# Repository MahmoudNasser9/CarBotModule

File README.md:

"# CarBotModule" 

<!-- Car Bot Moduls -->

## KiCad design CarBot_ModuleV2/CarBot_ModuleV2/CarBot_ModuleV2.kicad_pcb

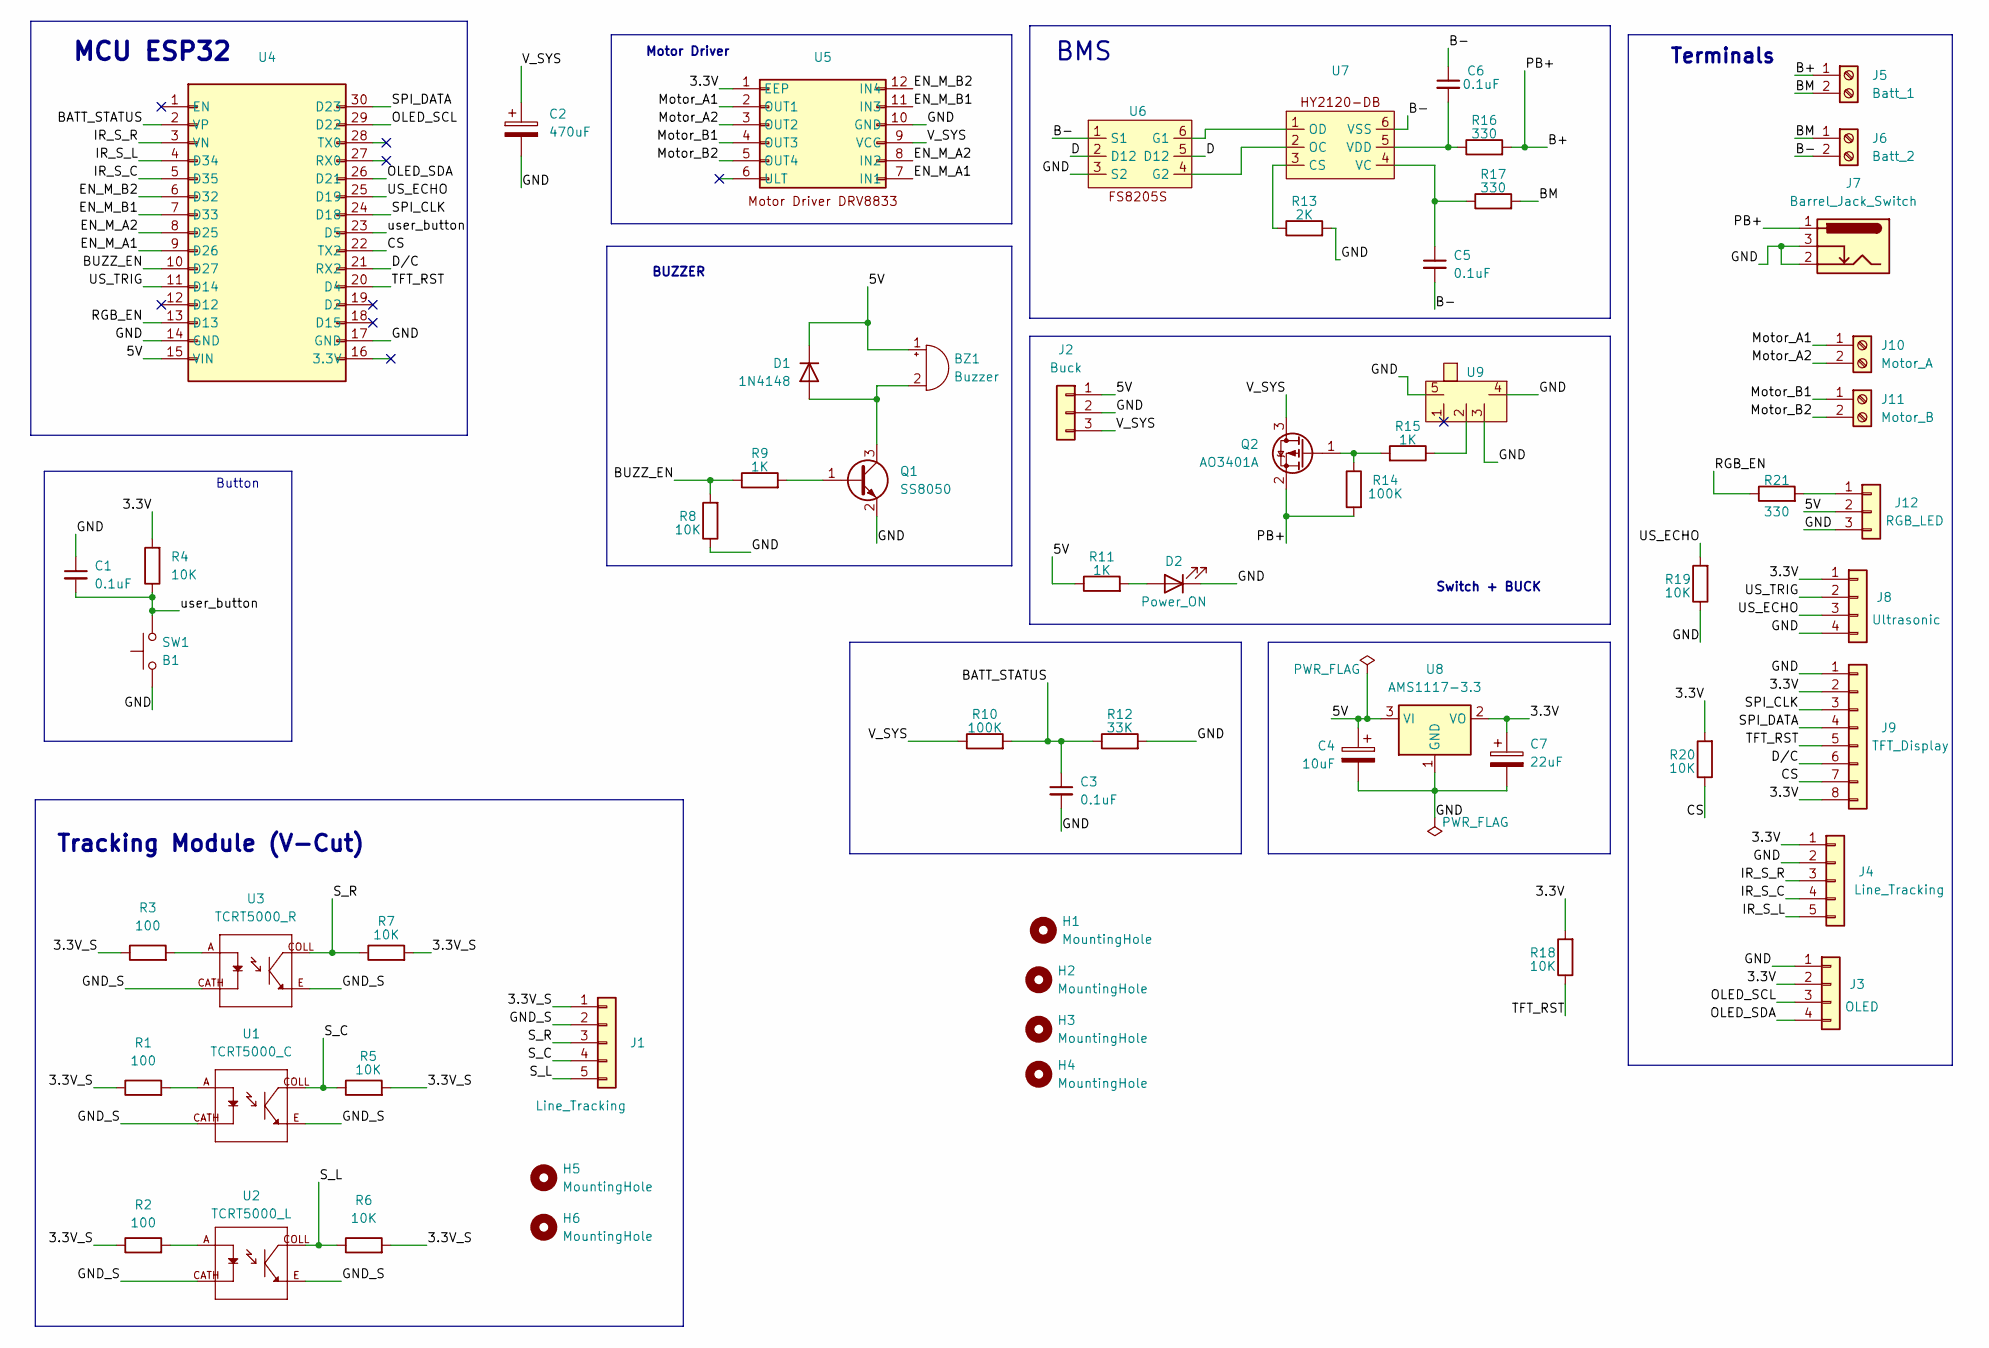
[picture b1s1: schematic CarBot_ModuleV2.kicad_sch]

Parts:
BZ1: Buzzer; Passive_Buzzer
C1, C3, C5, C6: 0.1uF; C_Disc_D5.0mm_W2.5mm_P2.50mm
C2: 470uF; CP_Radial_D10.0mm_P3.80mm
C4: 10uF; C_Radial_D5.0mm_H11.0mm_P2.00mm
C7: 22uF; C_Radial_D5.0mm_H11.0mm_P2.00mm
D1: 1N4148; D_DO-35_SOD27_P7.62mm_Horizontal
D2: Power_ON; LED_D3.0mm
H1, H2, H3, H4, H5, H6: MountingHole; MountingHole_3mm
J1, J4: Line_Tracking; JST_EH_B5B-EH-A_1x05_P2.50mm_Vertical
J2: Buck; Buck_farce
J3: OLED; PinHeader_1x04_P2.54mm_Vertical
J5: Batt_1; Pluggable Terminal Block 5.08-2P Right Angle
J6: Batt_2; Pluggable Terminal Block 5.08-2P Right Angle
J7: Barrel_Jack_Switch; BarrelJack_Horizontal
J8: Ultrasonic; PinHeader_1x04_P2.54mm_Vertical
J9: TFT_Display; JST_EH_B8B-EH-A_1x08_P2.50mm_Vertical
J10: Motor_A; Pluggable Terminal Block 5.08-2P Right Angle
J11: Motor_B; Pluggable Terminal Block 5.08-2P Right Angle
J12: RGB_LED; JST_XH_B3B-XH-A_1x03_P2.50mm_Vertical
Q1: SS8050; SOT-23_Handsoldering
Q2: AO3401A; SOT-23_Handsoldering
R1, R2, R3: 100; R_Axial_DIN0204_L3.6mm_D1.6mm_P7.62mm_Horizontal
R4, R5, R6, R7, R8, R18, R19, R20: 10K; R_Axial_DIN0204_L3.6mm_D1.6mm_P7.62mm_Horizontal
R9, R11, R15: 1K; R_Axial_DIN0204_L3.6mm_D1.6mm_P7.62mm_Horizontal
R10, R14: 100K; R_Axial_DIN0204_L3.6mm_D1.6mm_P7.62mm_Horizontal
R12: 33K; R_Axial_DIN0204_L3.6mm_D1.6mm_P7.62mm_Horizontal
R13: 2K; R_Axial_DIN0204_L3.6mm_D1.6mm_P7.62mm_Horizontal
R16, R17, R21: 330; R_Axial_DIN0204_L3.6mm_D1.6mm_P7.62mm_Horizontal
SW1: B1; SW_PUSH_6mm
U1: TCRT5000_C; TCRT5000
U2: TCRT5000_L; TCRT5000
U3: TCRT5000_R; TCRT5000
U4: ESP32-30pins
U5: MotDriver
U6, U7: SOT-23-6_Handsoldering
U8: AMS1117-3.3; SOT-89-3_Handsoldering
U9: Switch SPDT 3PIN 3mm Pin spacing

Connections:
/3.3V: C7.1, J3.2, J4.1, J8.1, J9.2, J9.8, R4.2, R18.2, R20.2, U5.1 (EEP), U8.2 (VO)
/3.3V_S: J1.1, R1.1, R2.1, R3.1, R5.2, R6.2, R7.2
/5V: BZ1.1 (+), C4.1, D1.1 (K), J2.1, J12.2, R11.1, U4.15 (VIN), U8.3 (VI)
/B+: J5.1, J7.1, Q2.2 (S), R14.2, R16.2
/B-: C5.2, C6.1, J6.2, U6.1 (S1), U7.6 (VSS)
/BATT_STATUS: C3.1, R10.2, R12.1, U4.2 (VP)
/BM: J5.2, J6.1, R17.2
/BUZZ_EN: R8.2, R9.1, U4.10 (D27)
/CS: J9.7, R20.1, U4.22 (TX2)
/D: U6.2 (D12), U6.5 (D12)
/D/C: J9.6, U4.21 (RX2)
/EN_M_A1: U4.9 (D26), U5.7 (IN1)
/EN_M_A2: U4.8 (D25), U5.8 (IN2)
/EN_M_B1: U4.7 (D33), U5.11 (IN3)
/EN_M_B2: U4.6 (D32), U5.12 (IN4)
/GND: C1.1, C2.2, C3.2, C4.2, C7.2, D2.1 (K), J2.2, J3.1, J4.2, J7.2, J7.3, J8.4, J9.1, J12.3, Q1.2 (E), R8.1, R12.2, R13.2, R19.1, SW1.1, U4.14 (GND), U4.17 (GND), U5.10 (GND), U6.3 (S2), U8.1 (GND), U9.3, U9.4, U9.5
/GND_S: J1.2, U1.CATH, U1.E, U2.CATH, U2.E, U3.CATH, U3.E
/IR_S_C: J4.4, U4.5 (D35)
/IR_S_L: J4.5, U4.4 (D34)
/IR_S_R: J4.3, U4.3 (VN)
/Motor_A1: J10.1, U5.2 (OUT1)
/Motor_A2: J10.2, U5.3 (OUT2)
/Motor_B1: J11.1, U5.4 (OUT3)
/Motor_B2: J11.2, U5.5 (OUT4)
/OLED_SCL: J3.3, U4.29 (D22)
/OLED_SDA: J3.4, U4.26 (D21)
/RGB_EN: R21.1, U4.13 (D13)
/SPI_CLK: J9.3, U4.24 (D18)
/SPI_DATA: J9.4, U4.30 (D23)
/S_C: J1.4, R5.1, U1.COLL
/S_L: J1.5, R6.1, U2.COLL
/S_R: J1.3, R7.1, U3.COLL
/TFT_RST: J9.5, R18.1, U4.20 (D4)
/US_ECHO: J8.3, R19.2, U4.25 (D19)
/US_TRIG: J8.2, U4.11 (D14)
/V_SYS: C2.1, J2.3, Q2.3 (D), R10.1, U5.9 (VCC)
/user_button: C1.2, R4.1, SW1.2, U4.23 (D5)
unnamed: BZ1.2 (-), D1.2 (A), Q1.3 (C)
unnamed: D2.2 (A), R11.2
unnamed: J12.1, R21.2
unnamed: Q1.1 (B), R9.2
unnamed: Q2.1 (G), R14.1, R15.2
unnamed: R1.2, U1.A
unnamed: R2.2, U2.A
unnamed: R3.2, U3.A
unnamed: R15.1, U9.2
unnamed: U6.6 (G1), U7.1 (OD)
unnamed: U6.4 (G2), U7.2 (OC)
unnamed: R13.1, U7.3 (CS)
unnamed: C5.1, R17.1, U7.4 (VC)
unnamed: C6.2, R16.1, U7.5 (VDD)

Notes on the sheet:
Tracking Module (V-Cut)
Motor Driver
Switch + BUCK
BMS
Button
BUZZER
MCU ESP32
Terminals

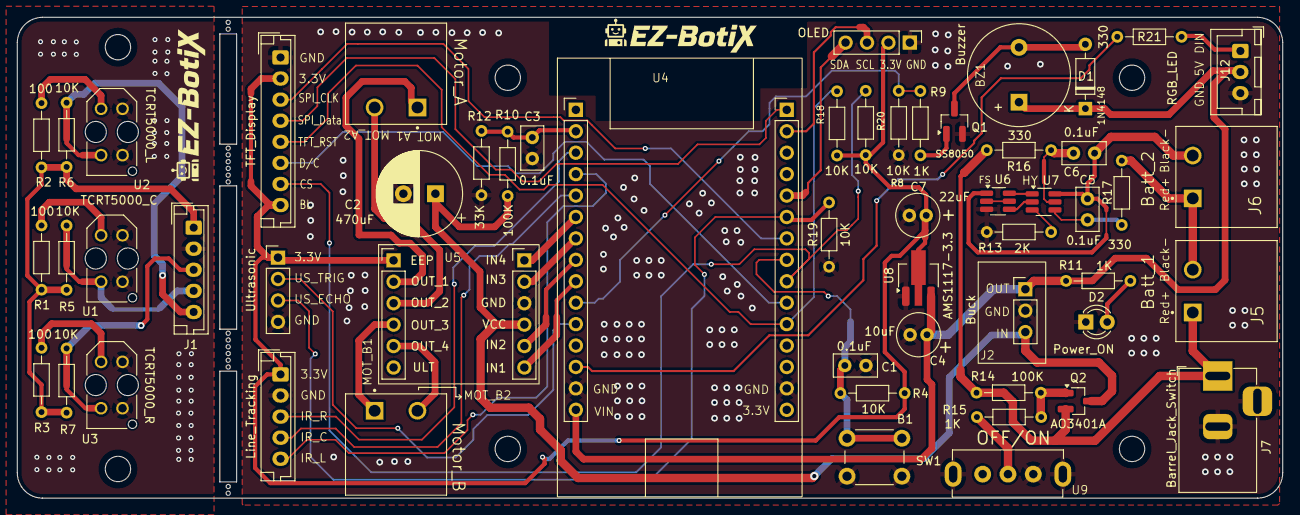
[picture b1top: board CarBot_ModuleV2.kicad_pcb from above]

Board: 2 copper layers, 150.0 x 57.0 mm, 61 parts (0 on the bottom side), 51 nets.

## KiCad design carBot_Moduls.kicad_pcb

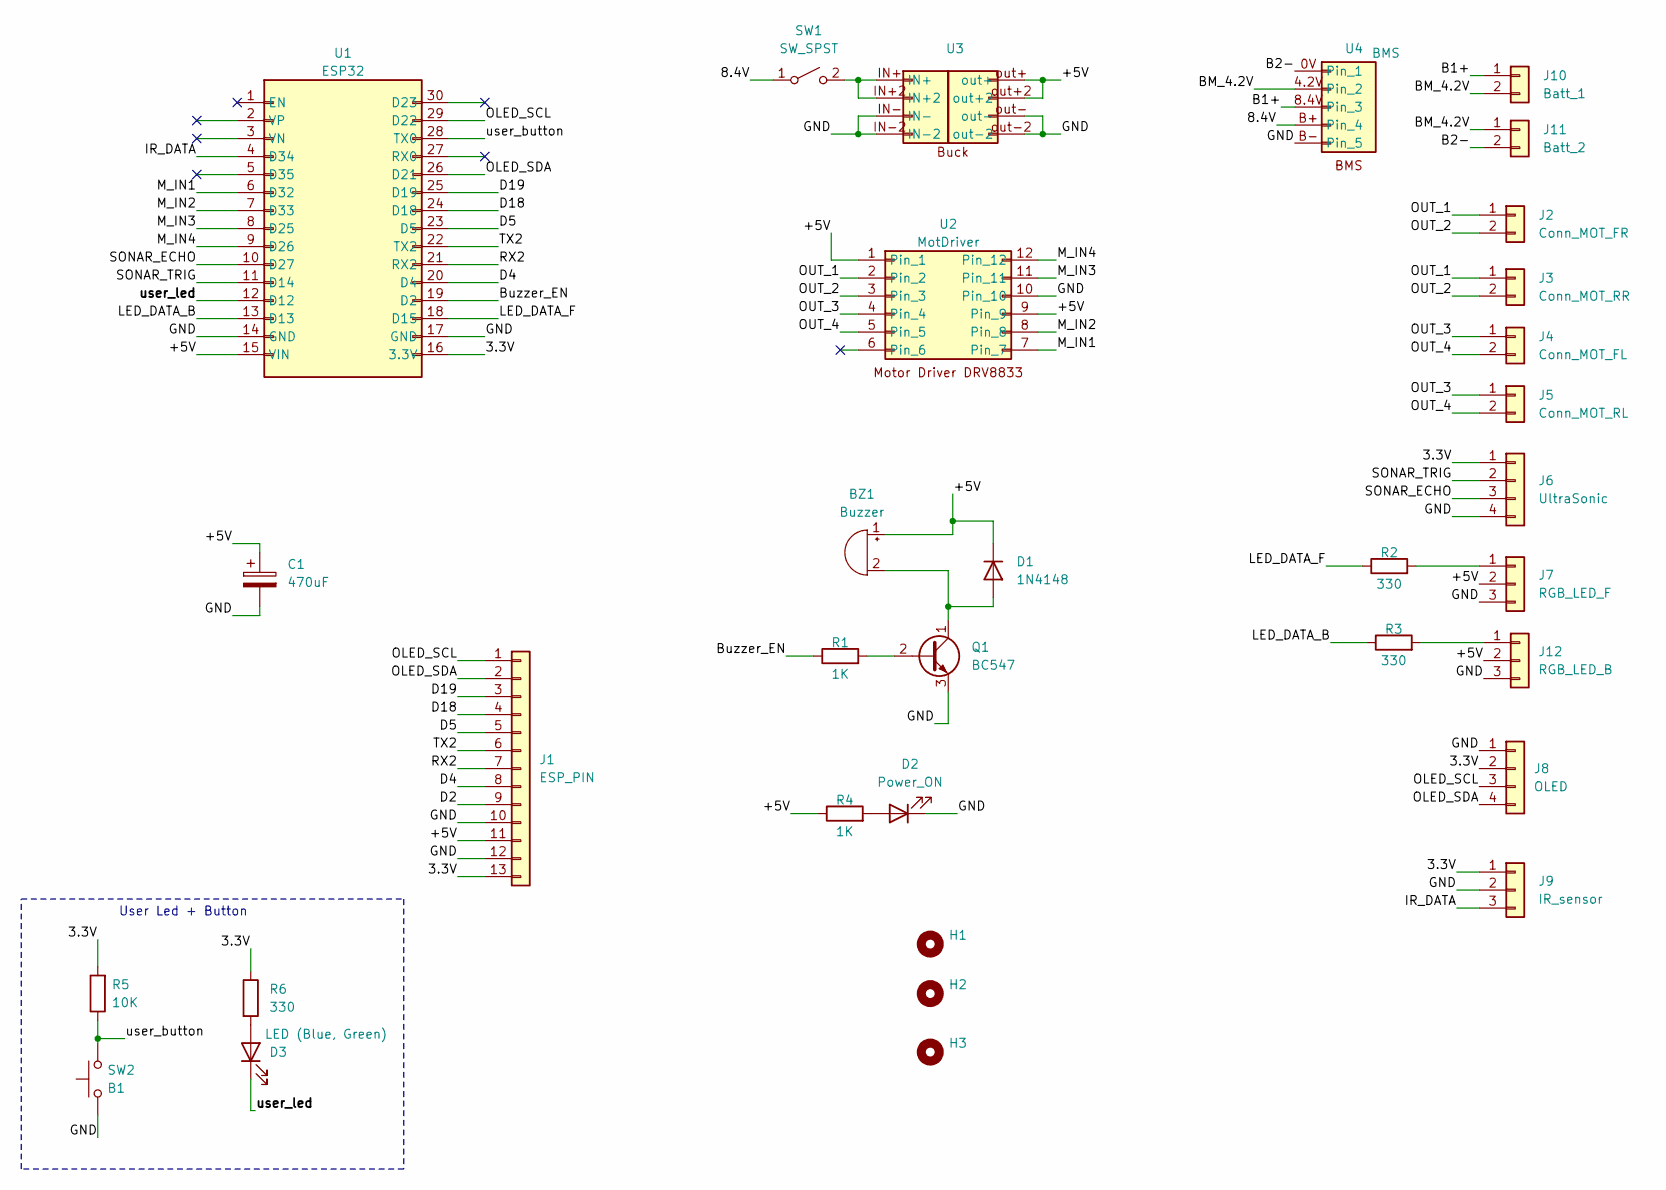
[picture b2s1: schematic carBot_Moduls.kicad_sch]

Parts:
BZ1: Buzzer; Buzzer_12x9.5RM7.6
C1: 470uF; CP_Radial_D5.0mm_P2.50mm
D1: 1N4148; D_DO-35_SOD27_P7.62mm_Horizontal
D2: Power_ON; LED_D3.0mm
D3: LED (Blue, Green); LED_D3.0mm
H1, H2, H3: MountingHole_3mm
J1: ESP_PIN; PinHeader_1x13_P2.54mm_Vertical
J2: Conn_MOT_FR; JST_XH_B2B-XH-A_1x02_P2.50mm_Vertical
J3: Conn_MOT_RR; JST_XH_B2B-XH-A_1x02_P2.50mm_Vertical
J4: Conn_MOT_FL; JST_XH_B2B-XH-A_1x02_P2.50mm_Vertical
J5: Conn_MOT_RL; JST_XH_B2B-XH-A_1x02_P2.50mm_Vertical
J6: UltraSonic; JST_XH_B4B-XH-A_1x04_P2.50mm_Vertical
J7: RGB_LED_F; JST_XH_B3B-XH-A_1x03_P2.50mm_Vertical
J8: OLED; JST_XH_B4B-XH-A_1x04_P2.50mm_Vertical
J9: IR_sensor; JST_XH_B3B-XH-A_1x03_P2.50mm_Vertical
J10: Batt_1; JST_XH_B2B-XH-A_1x02_P2.50mm_Vertical
J11: Batt_2; JST_XH_B2B-XH-A_1x02_P2.50mm_Vertical
J12: RGB_LED_B; JST_XH_B3B-XH-A_1x03_P2.50mm_Vertical
Q1: BC547; TO-92_Inline
R1, R4: 1K; R_Axial_DIN0204_L3.6mm_D1.6mm_P7.62mm_Horizontal
R2, R3, R6: 330; R_Axial_DIN0204_L3.6mm_D1.6mm_P7.62mm_Horizontal
R5: 10K; R_Axial_DIN0204_L3.6mm_D1.6mm_P7.62mm_Horizontal
SW1: SW_SPST; KCD1-11_ON_OFF
SW2: B1; SW_PUSH_6mm
U1: ESP32; ESP32-30pins
U2: MotDriver
U3: Buck
U4: BMS

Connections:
/3.3V: J1.13, J6.1, J8.2, J9.1, R5.2, R6.1, U1.16 (3.3V)
/8.4V: SW1.1 (A), U4.B+ (Pin_4)
/+5V: BZ1.1 (+), C1.1, D1.1 (K), J1.11, J7.2, J12.2, R4.1, U1.15 (VIN), U2.1, U2.9, U3.out+, U3.out+2
/B1+: J10.1, U4.8.4V (Pin_3)
/B2-: J11.2, U4.0V (Pin_1)
/BM_4.2V: J10.2, J11.1, U4.4.2V (Pin_2)
/D4: J1.8, U1.20 (D4)
/D5: J1.5, U1.23 (D5)
/D18: J1.4, U1.24 (D18)
/D19: J1.3, U1.25 (D19)
/GND: C1.2, D2.1 (K), J1.10, J1.12, J6.4, J7.3, J8.1, J9.2, J12.3, Q1.3 (E), SW2.1, U1.14 (GND), U1.17 (GND), U2.10, U3.IN-, U3.IN-2, U3.out-, U3.out-2, U4.B- (Pin_5)
/IR_DATA: J9.3, U1.4 (D34)
/LED_DATA_B: R3.1, U1.13 (D13)
/LED_DATA_F: R2.1, U1.18 (D15)
/M_IN1: U1.6 (D32), U2.7
/M_IN2: U1.7 (D33), U2.8
/M_IN3: U1.8 (D25), U2.11
/M_IN4: U1.9 (D26), U2.12
/OLED_SCL: J1.1, J8.3, U1.29 (D22)
/OLED_SDA: J1.2, J8.4, U1.26 (D21)
/OUT_1: J2.1, J3.1, U2.2
/OUT_2: J2.2, J3.2, U2.3
/OUT_3: J4.1, J5.1, U2.4
/OUT_4: J4.2, J5.2, U2.5
/RX2: J1.7, U1.21 (RX2)
/SONAR_ECHO: J6.3, U1.10 (D27)
/SONAR_TRIG: J6.2, U1.11 (D14)
/TX2: J1.6, U1.22 (TX2)
/user_button: R5.1, SW2.2, U1.28 (TX0)
/user_led: D3.1 (K), U1.12 (D12)
unnamed: BZ1.2 (-), D1.2 (A), Q1.1 (C)
unnamed: D2.2 (A), R4.2
unnamed: D3.2 (A), R6.2
unnamed: J7.1, R2.2
unnamed: J12.1, R3.2
unnamed: Q1.2 (B), R1.2
unnamed: SW1.2 (B), U3.IN+, U3.IN+2

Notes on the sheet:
User Led + Button

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
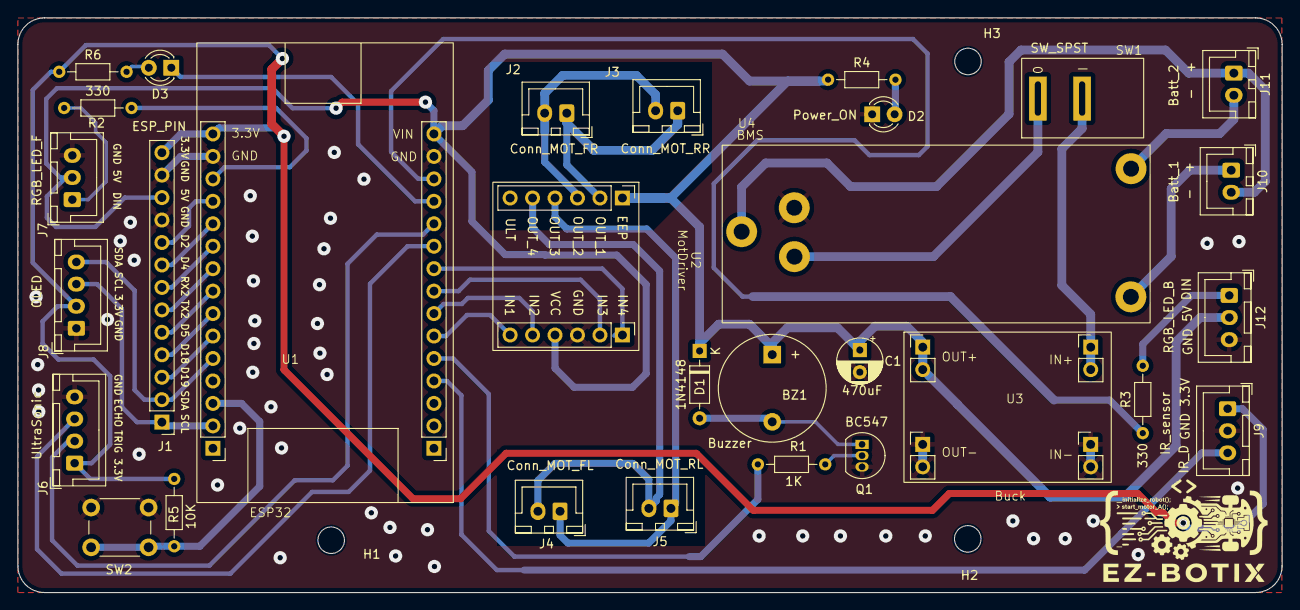
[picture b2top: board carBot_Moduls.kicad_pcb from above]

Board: 2 copper layers, 143.0 x 65.0 mm, 33 parts (0 on the bottom side), 39 nets.
